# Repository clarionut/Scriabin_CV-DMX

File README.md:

# Scriabin_CV-DMX

A two channel CV-DMX converter based on an Arduino Pro Mini microcontroller.

Named for the famously synaesthetic composer Scriabin, this module was designed to allow RGB LED PAR cans to be voltage controlled by an analogue modular synthesiser.
Each of the two channels can be controlled in the RGB (red, green, blue) or HSV (hue, saturation, value) colourspace, giving three control inputs per channel.
Each individual input has an attenuator for the CV input and an initial value potentiometer, so all colours are accessible without using the CV inputs.
In RGB mode the inputs control the red, green and blue channels individually, simple to understand but harder to use. Consequently HSV is probably the more useful colourspace, where setting the saturation and value initial values to maximum allows all hues to be accessed using just one CV input. This is also the reason for using HSV rather than the HSL (hue, saturation, lightness) colourspace, where the fully saturated colours are found at 100% saturation, 50% lightness.

There is also a 'hidden' mode on each channel (hidden mainly because of lack of space on the panel!). With the mode switch in the centre-off position the corresponding
channel will enter 'Scriabin mode' which converts the incoming Red/Hue CV into quantised light colours according to the scheme used by Scriabin in his ['Clavier à lumières'](https://en.wikipedia.org/wiki/Clavier_%C3%A0_lumi%C3%A8res).
The colours are: C - red; C# - purple; D - yellow; D# - flesh; E - sky blue; F - deep red; F# - bright blue; G - orange; G# - lilac; A - green; A# - rose; B - blue (this makes more sense if ordered by the circle of fifths - C - red; G - orange; D - yellow; A - green; E - sky blue; B - blue; F# - bright blue; C# - purple; G# - lilac; D# - flesh; A# - rose; F - deep red).
In this mode the input CV range should be adjusted so that successive octaves give the same colour. The tracking isn't perfect but should be good over about 2 1/2 octaves.
The Green/Saturation control has no effect in this mode but the Blue/Value control can be used to fade the light in and out, though the colours are increasingly inaccurate at low brightness.

The hardware is based on an Arduino Pro Mini driving a MAX485 RS-485 transceiver chip, as used in some of the commercial Arduino DMX shields.
The CV inputs have protection against out-of-range voltage inputs, but there is no isolation on the MAX485 (again like many of the commercial DMX shields).
Consequently the synthesiser and the light units must be powered from the same electrical circuit to avoid potentially dangerous voltages entering the synth.

The KiCad schematic and board layout use some custom symbols and footprints, so you will need to add my [kiCad_libraries](https://github.com/clarionut/kiCad_libraries)
before using these files.

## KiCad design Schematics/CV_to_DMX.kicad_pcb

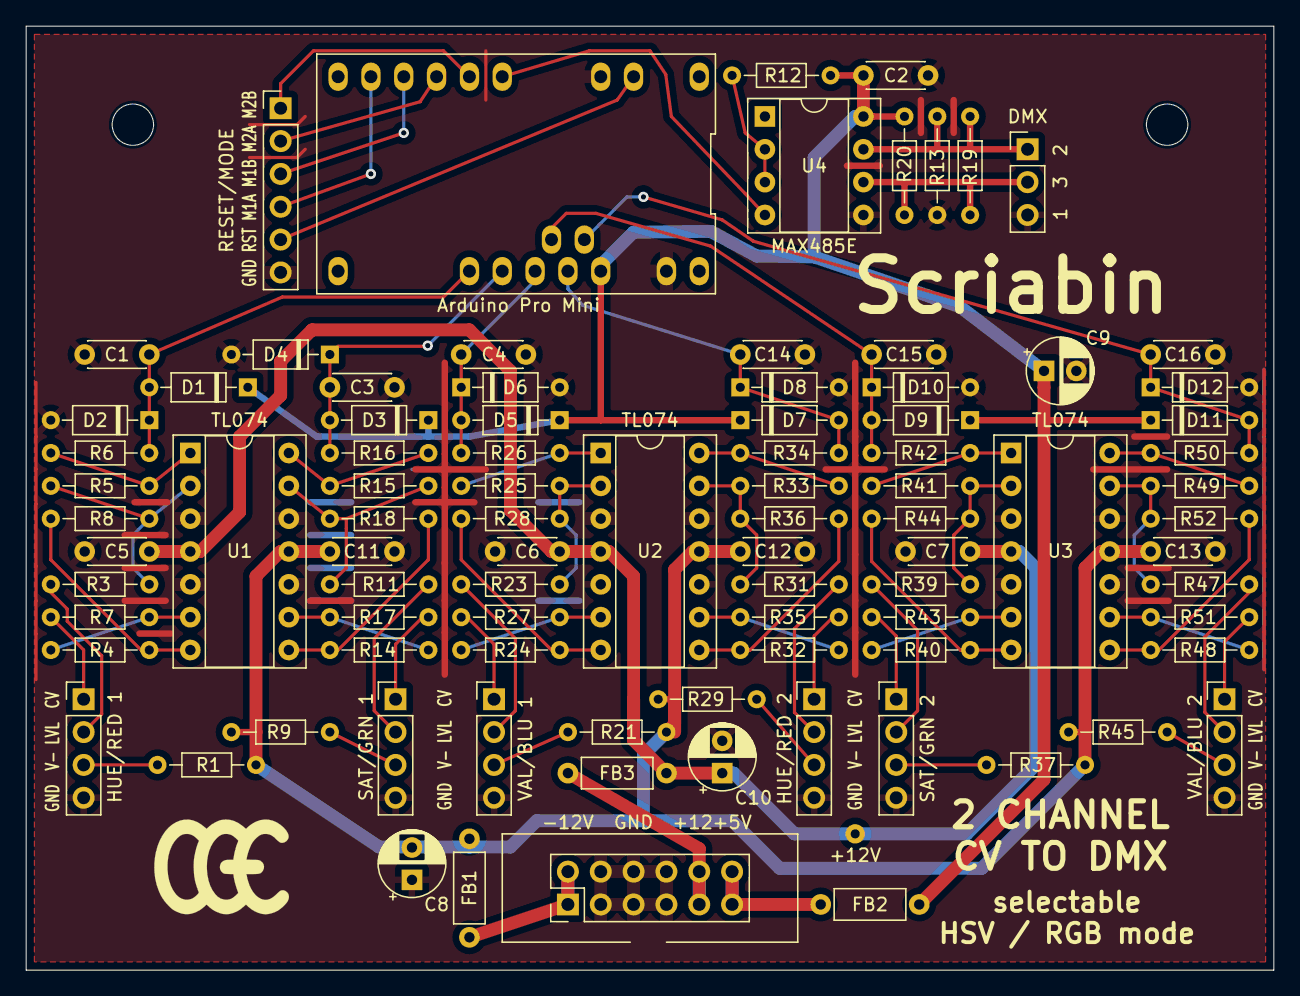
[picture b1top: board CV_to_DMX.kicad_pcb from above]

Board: 2 copper layers, 96.5 x 73.0 mm, 92 parts (0 on the bottom side), 64 nets.

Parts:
+12V: +12V; TestPoint_THTPad_1.5x1.5mm_Drill0.7mm
A1: Arduino_Pro_Mini
C1, C3, C4, C14, C15, C16: 10n; C_Disc_D4.3mm_W1.9mm_P5.00mm
C2, C5, C6, C7, C11, C12, C13: 100n; C_Disc_D4.3mm_W1.9mm_P5.00mm
C8, C9, C10: 10u; CP_Radial_D5.0mm_P2.50mm
D1, D2, D3, D4, D5, D6, D7, D8, D9, D10, D11, D12: BAT43; D_DO-35_SOD27_P7.62mm_Horizontal
FB1, FB2, FB3: FB; L_Axial_L5.3mm_D2.2mm_P7.62mm_Horizontal_Vishay_IM-1
J1: CHNL1; PinHeader_1x04_P2.54mm_Vertical
J3: RESET/MODE; PinHeader_1x06_P2.54mm_Vertical
J4: CHNL2; PinHeader_1x04_P2.54mm_Vertical
J7: CHNL3; PinHeader_1x04_P2.54mm_Vertical
J9: POWER; Power_2x06
J10: CHNL4; PinHeader_1x04_P2.54mm_Vertical
J12: CHNL5; PinHeader_1x04_P2.54mm_Vertical
J14: CHNL6; PinHeader_1x04_P2.54mm_Vertical
J16: DMX; PinHeader_1x03_P2.54mm_Vertical
R1, R9, R12, R13, R20, R21, R29, R37, R45: 10k; R_Axial_DIN0204_L3.6mm_D1.6mm_P7.62mm_Horizontal
R3, R4, R11, R14, R23, R24, R31, R32, R39, R40, R47, R48: 200k; R_Axial_DIN0204_L3.6mm_D1.6mm_P7.62mm_Horizontal
R5, R7, R8, R15, R17, R18, R25, R27, R28, R33, R35, R36, R41, R43, R44, R49, R51, R52: 100k; R_Axial_DIN0204_L3.6mm_D1.6mm_P7.62mm_Horizontal
R6, R16, R26, R34, R42, R50: 47k; R_Axial_DIN0204_L3.6mm_D1.6mm_P7.62mm_Horizontal
R19: 120R?; R_Axial_DIN0204_L3.6mm_D1.6mm_P7.62mm_Horizontal
U1, U2, U3: TL074; DIP-14_W7.62mm_Socket
U4: MAX485E; DIP-8_W7.62mm_Socket

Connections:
+5V: A1.21 (VCC), C2.1, C9.1, D1.1 (K), D3.1 (K), D5.1 (K), D7.1 (K), D9.1 (K), D11.1 (K), FB2.1, R12.1, R20.1, U4.8 (VCC)
+12V: +12V.1, C5.1, C6.1, C7.1, C10.1, FB3.1, U1.4 (V+), U2.4 (V+), U3.4 (V+)
-12V: C8.2, C11.1, C12.1, C13.1, FB1.1, R1.1, R9.1, R21.1, R29.1, R37.1, R45.1, U1.11 (V-), U2.11 (V-), U3.11 (V-)
/A: J16.2, R19.1, R20.2, U4.6 (A)
/A0: A1.17 (A0), C1.1, D1.2 (A), D2.1 (K), R6.1
/A1: A1.18 (A1), C3.1, D3.2 (A), D4.1 (K), R16.1
/A2: A1.19 (A2), C4.1, D5.2 (A), D6.1 (K), R26.1
/B: J16.1, R13.2, R19.2, U4.7 (B)
/CV1: J1.1, R7.2
/CV2: J4.1, R17.2
/CV3: J7.1, R27.2
/Channel2/A3: A1.20 (A3), C14.1, D7.2 (A), D8.1 (K), R34.1
/Channel2/A4: A1.25 (A4), C15.1, D9.2 (A), D10.1 (K), R42.1
/Channel2/A5: A1.26 (A5), C16.1, D11.2 (A), D12.1 (K), R50.1
/Channel2/CV4: J10.1, R35.2
/Channel2/CV5: J12.1, R43.2
/Channel2/CV6: J14.1, R51.2
/Channel2/OS4: J10.2, R31.1
/Channel2/OS5: J12.2, R39.1
/Channel2/OS6: J14.2, R47.1
/Channel2/V-4: J10.3, R29.2
/Channel2/V-5: J12.3, R37.2
/Channel2/V-6: J14.3, R45.2
/D4: A1.7 (D4), U4.4 (DI)
/D5: A1.8 (D5), J3.1
/D6: A1.9 (D6), J3.2
/D7: A1.10 (D7), J3.3
/D8: A1.11 (D8), J3.4
/OS1: J1.2, R3.1
/OS2: J4.2, R11.1
/OS3: J7.2, R23.1
/RST: A1.3 (RST), J3.5
/V-1: J1.3, R1.2
/V-2: J4.3, R9.2
/V-3: J7.3, R21.2
GND: A1.4 (GND), A1.23 (GND), C1.2, C2.2, C3.2, C4.2, C5.2, C6.2, C7.2, C8.1, C9.2, C10.2, C11.2, C12.2, C13.2, C14.2, C15.2, C16.2, D2.2 (A), D4.2 (A), D6.2 (A), D8.2 (A), D10.2 (A), D12.2 (A), J1.4, J3.6, J4.4, J7.4, J9.3, J9.4, J9.5, J9.6, J9.7, J9.8, J10.4, J12.4, J14.4, J16.3, R13.1, U1.3 (+), U1.5 (+), U1.10 (+), U1.12 (+), U2.3 (+), U2.5 (+), U2.10 (+), U2.12 (+), U3.3 (+), U3.5 (+), U3.10 (+), U3.12 (+), U4.5 (GND)
unnamed: FB1.2, J9.1, J9.2
unnamed: FB3.2, J9.9, J9.10
unnamed: FB2.2, J9.11, J9.12
unnamed: R4.1, R8.2, U1.7
unnamed: R5.1, R6.2, U1.1
unnamed: R14.1, R18.2, U1.8
unnamed: R15.1, R16.2, U1.14
unnamed: R24.1, R28.2, U2.7
unnamed: R25.1, R26.2, U2.1
unnamed: R32.1, R36.2, U2.8
unnamed: R33.1, R34.2, U2.14
unnamed: R40.1, R44.2, U3.7
unnamed: R41.1, R42.2, U3.1
unnamed: R48.1, R52.2, U3.8
unnamed: R49.1, R50.2, U3.14
unnamed: R3.2, R5.2, R8.1, U1.2 (-)
unnamed: R4.2, R7.1, U1.6 (-)
unnamed: R14.2, R17.1, U1.9 (-)
unnamed: R11.2, R15.2, R18.1, U1.13 (-)
unnamed: R23.2, R25.2, R28.1, U2.2 (-)
unnamed: R24.2, R27.1, U2.6 (-)
unnamed: R32.2, R35.1, U2.9 (-)
unnamed: R31.2, R33.2, R36.1, U2.13 (-)
unnamed: R39.2, R41.2, R44.1, U3.2 (-)
unnamed: R40.2, R43.1, U3.6 (-)
unnamed: R48.2, R51.1, U3.9 (-)
unnamed: R47.2, R49.2, R52.1, U3.13 (-)
unnamed: R12.2, U4.2 (~RE), U4.3 (DE)

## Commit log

2024-07-02 Create temp
